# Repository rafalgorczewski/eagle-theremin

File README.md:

# eagle-theremin
A simple theremin board designed in Eagle.

Board           |  Schematic
:-------------------------:|:-------------------------:
  |

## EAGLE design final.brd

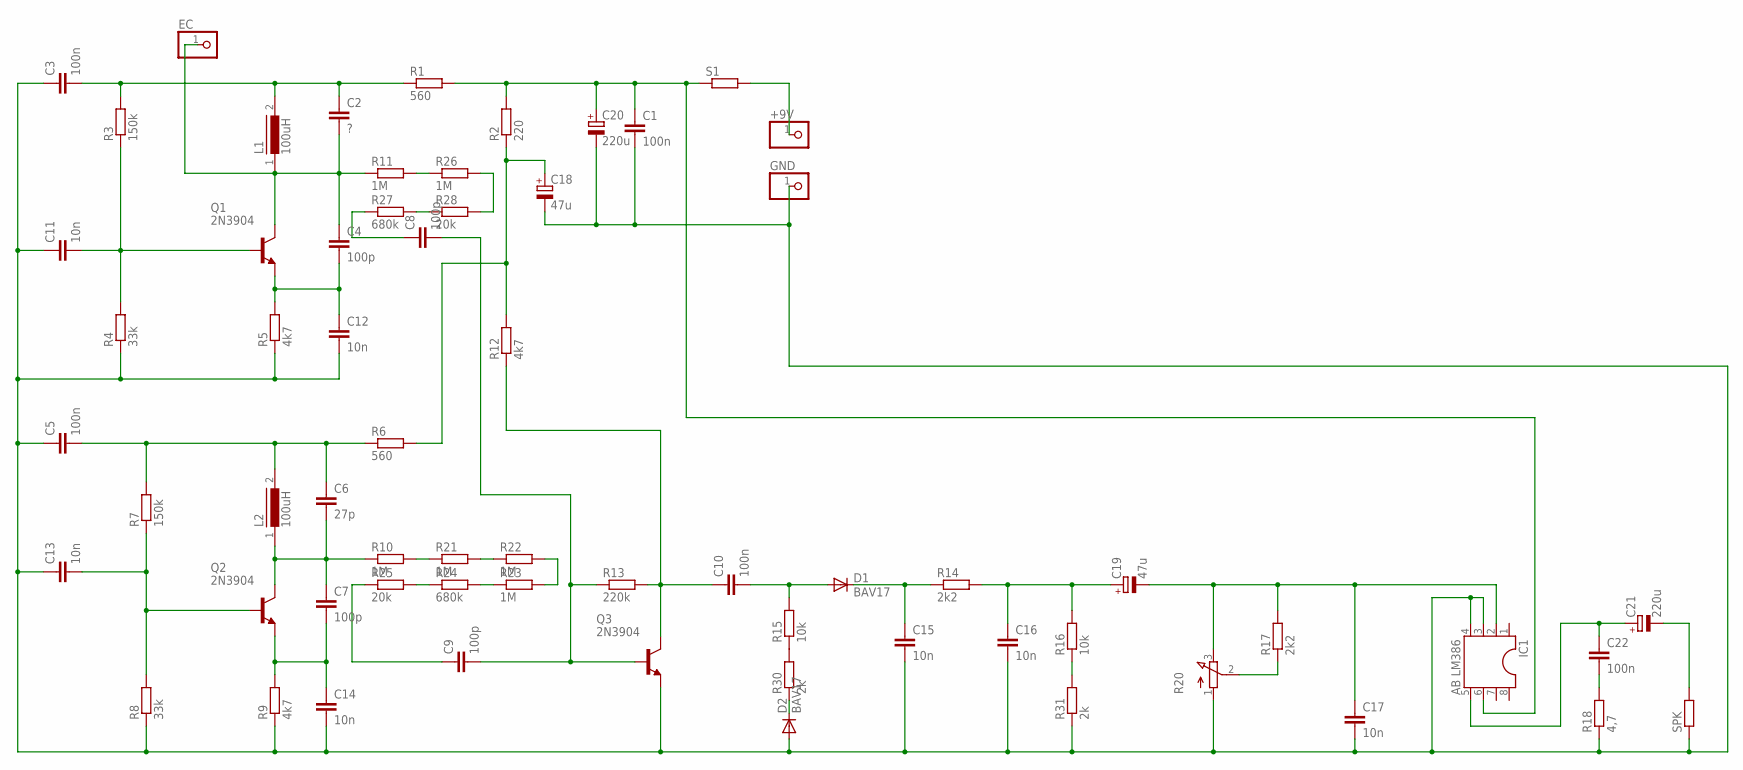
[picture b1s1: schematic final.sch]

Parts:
+9V: PINHD-1X1; 1X01
C1, C3, C5, C10, C22: 100n; C025-025X050
C2: ?; C025-025X050
C4, C7, C8, C9: 100p; C025-025X050
C6: 27p; C025-025X050
C11, C12, C13, C14, C15, C16, C17: 10n; C050-025X075
C18, C19: 47u; E5-6
C20, C21: 220u; E5-8,5
D1, D2: BAV17; DO35-10
EC: PINHD-1X1; 1X01
GND: PINHD-1X1; 1X01
IC1: AB LM386; DIL08
L1, L2: 100uH; 82114R
Q1, Q2, Q3: 2N3904; TO92
R1, R6: 560; 0204/5
R2: 220; 0204/5
R3, R7: 150k; 0204/5
R4, R8: 33k; 0204/5
R5, R9, R12: 4k7; 0204/5
R10, R11, R21, R22, R23, R26: 1M; 0204/5
R13: 220k; 0204/5
R14, R17: 2k2; 0204/5
R15, R16: 10k; 0204/5
R18: 4,7; 0204/5
R20: 3RP/1610N
R24, R27: 680k; 0204/5
R25, R28: 20k; 0204/5
R30, R31: 2k; 0204/5
S1: R-EU_0204/5; 0204/5
SPK: R-EU_0204/5; 0204/5

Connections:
unnamed: C1.1, C20.+, IC1.6, R1.2, R2.2, S1.1
unnamed: C21.+, C22.1, IC1.5
unnamed: C13.2, Q2.2 (B), R7.1, R8.2
unnamed: C2.1, C3.2, L1.2, R1.1, R3.2
unnamed: C2.2, C4.1, EC.1, L1.1, Q1.1 (C), R11.1
unnamed: C17.1, C19.-, IC1.2, R17.2, R20.3 (E)
unnamed: C11.2, Q1.2 (B), R3.1, R4.2
unnamed: C4.2, C12.1, Q1.3 (E), R5.2
unnamed: R15.1, R30.2
unnamed: R17.1, R20.2 (S)
unnamed: C5.2, C6.1, L2.2, R6.1, R7.2
unnamed: C7.2, C14.1, Q2.3 (E), R9.2
unnamed: C6.2, C7.1, L2.1, Q2.1 (C), R10.1
unnamed: R10.2, R21.1
unnamed: R21.2, R22.1
unnamed: R22.2, R23.2
unnamed: R23.1, R24.2
unnamed: R24.1, R25.2
unnamed: C9.1, R25.1
unnamed: R11.2, R26.1
unnamed: R26.2, R28.2
unnamed: R27.2, R28.1
unnamed: C8.1, R27.1
unnamed: C8.2, C9.2, Q3.2 (B), R13.1
unnamed: C18.+, R2.1, R6.2, R12.2
unnamed: C10.1, Q3.1 (C), R12.1, R13.2
unnamed: C10.2, D1.A, R15.2
unnamed: D2.C, R30.1
unnamed: C15.1, D1.C, R14.1
unnamed: C16.1, C19.+, R14.2, R16.2
unnamed: C21.-, SPK.2
unnamed: C22.2, R18.2
unnamed: R16.1, R31.2
unnamed: +9V.1, S1.2
unnamed: C1.2, C3.1, C5.1, C11.1, C12.2, C13.1, C14.2, C15.2, C16.2, C17.2, C18.-, C20.-, D2.A, GND.1, IC1.3, IC1.4, Q3.3 (E), R4.1, R5.1, R8.1, R9.1, R18.1, R20.1 (A), R31.1, SPK.1

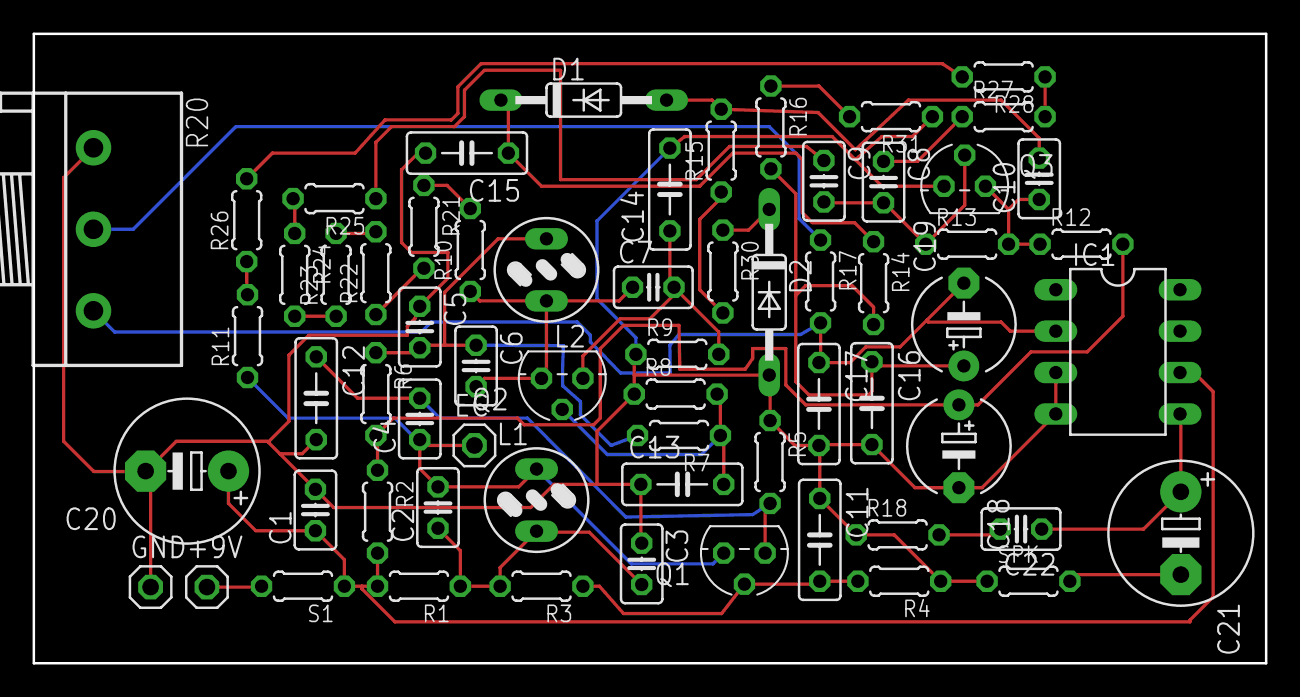
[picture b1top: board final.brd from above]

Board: 2 copper layers, 75.6 x 38.6 mm, 64 parts (0 on the bottom side), 35 nets.
